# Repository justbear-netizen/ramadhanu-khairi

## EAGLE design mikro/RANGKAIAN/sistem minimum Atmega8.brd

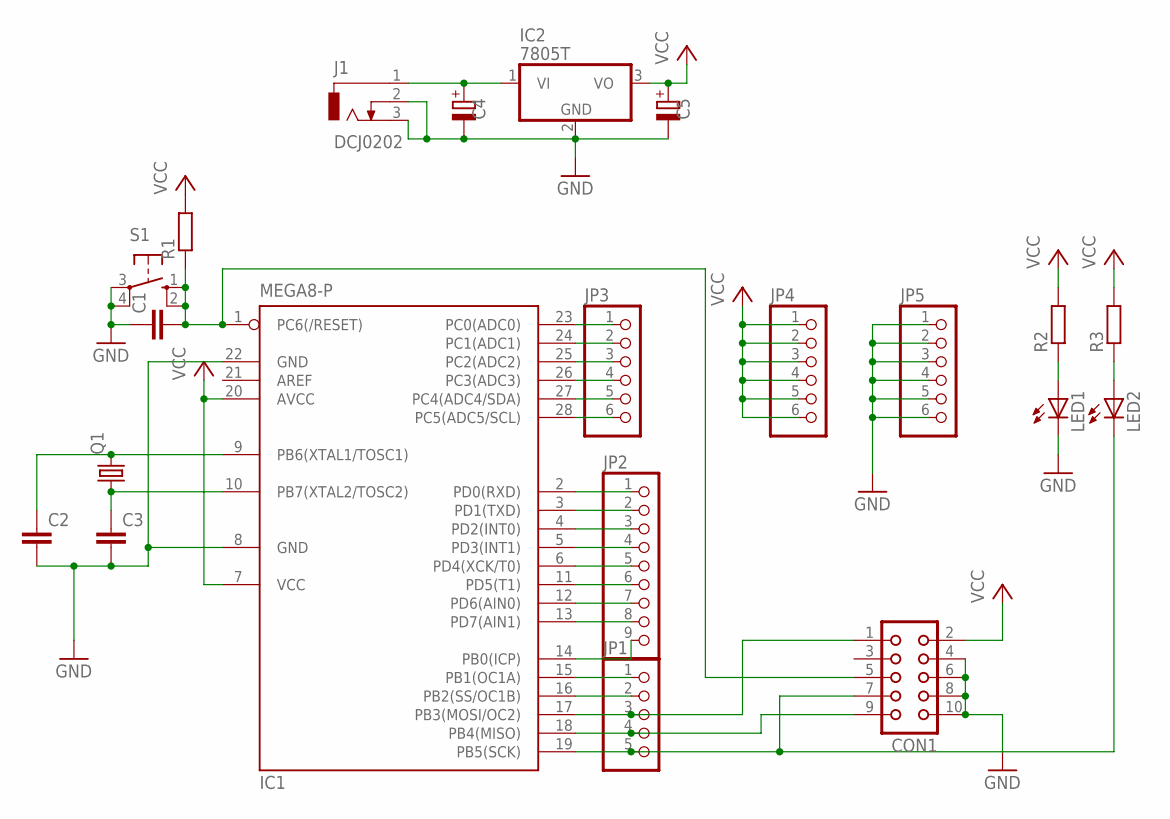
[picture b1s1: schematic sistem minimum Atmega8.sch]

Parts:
C1, C2, C3: C-EU025-030X050; C025-030X050
C4, C5: CPOL-EUE2.5-6; E2,5-6
CON1: CON10
IC1: MEGA8-P; DIL28-3
IC2: 7805T; TO220H
J1: DCJ0202
JP1: PINHD-1X5; 1X05
JP2: PINHD-1X9; 1X09
JP3, JP4, JP5: PINHD-1X6; 1X06
LED1, LED2: LED3MM
Q1: CRYSTALHC49U-V; HC49U-V
R1, R2, R3: R-EU_0204/7; 0204/7
S1: 10-XX; B3F-10XX

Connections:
GND: C1.1, C2.2, C3.2, C4.-, C5.-, CON1.4, CON1.6, CON1.8, CON1.10, IC1.8 (GND), IC1.22 (GND), IC2.2 (GND), J1.2, J1.3, JP5.1, JP5.2, JP5.3, JP5.4, JP5.5, JP5.6, LED1.K (C), S1.3, S1.4 (P1)
unnamed: IC1.2 (PD0(RXD)), JP2.1
unnamed: IC1.3 (PD1(TXD)), JP2.2
unnamed: IC1.4 (PD2(INT0)), JP2.3
unnamed: IC1.5 (PD3(INT1)), JP2.4
unnamed: IC1.6 (PD4(XCK/T0)), JP2.5
unnamed: IC1.11 (PD5(T1)), JP2.6
unnamed: IC1.12 (PD6(AIN0)), JP2.7
unnamed: IC1.13 (PD7(AIN1)), JP2.8
unnamed: IC1.14 (PB0(ICP)), JP2.9
unnamed: IC1.15 (PB1(OC1A)), JP1.1
unnamed: IC1.16 (PB2(SS/OC1B)), JP1.2
unnamed: CON1.1, IC1.17 (PB3(MOSI/OC2)), JP1.3
unnamed: CON1.9, IC1.18 (PB4(MISO)), JP1.4
unnamed: C4.+, IC2.1 (VI), J1.1
unnamed: IC1.23 (PC0(ADC0)), JP3.1
unnamed: IC1.24 (PC1(ADC1)), JP3.2
unnamed: IC1.25 (PC2(ADC2)), JP3.3
unnamed: IC1.26 (PC3(ADC3)), JP3.4
unnamed: IC1.27 (PC4(ADC4/SDA)), JP3.5
unnamed: IC1.28 (PC5(ADC5/SCL)), JP3.6
unnamed: C2.1, IC1.9 (PB6(XTAL1/TOSC1)), Q1.2
unnamed: C3.1, IC1.10 (PB7(XTAL2/TOSC2)), Q1.1
unnamed: C1.2, CON1.5, IC1.1 (PC6(/RESET)), R1.1, S1.1 (S), S1.2 (S1)
unnamed: LED2.A, R3.1
unnamed: CON1.7, IC1.19 (PB5(SCK)), JP1.5, LED2.K (C)
unnamed: LED1.A, R2.1
VCC: C5.+, CON1.2, IC1.7 (VCC), IC1.20 (AVCC), IC2.3 (VO), JP4.1, JP4.2, JP4.3, JP4.4, JP4.5, JP4.6, R1.2, R2.2, R3.2

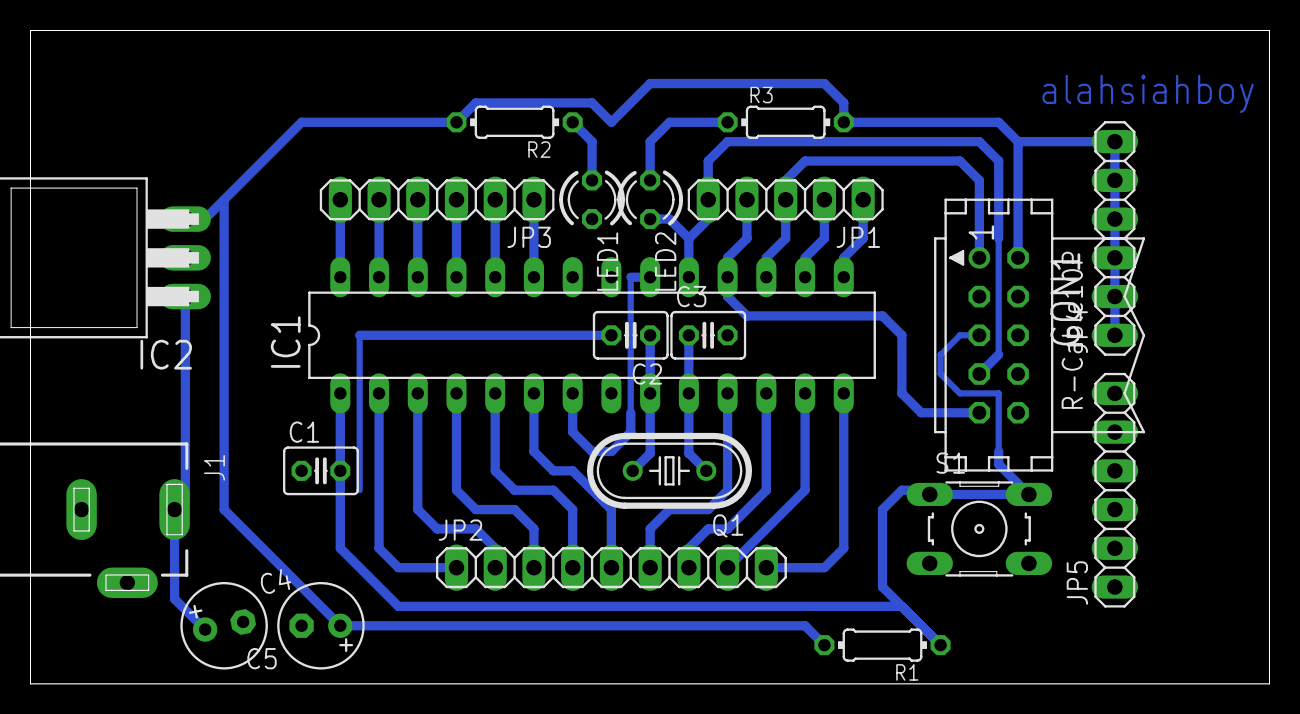
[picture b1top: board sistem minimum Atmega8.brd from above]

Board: 2 copper layers, 81.3 x 42.9 mm, 21 parts (0 on the bottom side), 28 nets.

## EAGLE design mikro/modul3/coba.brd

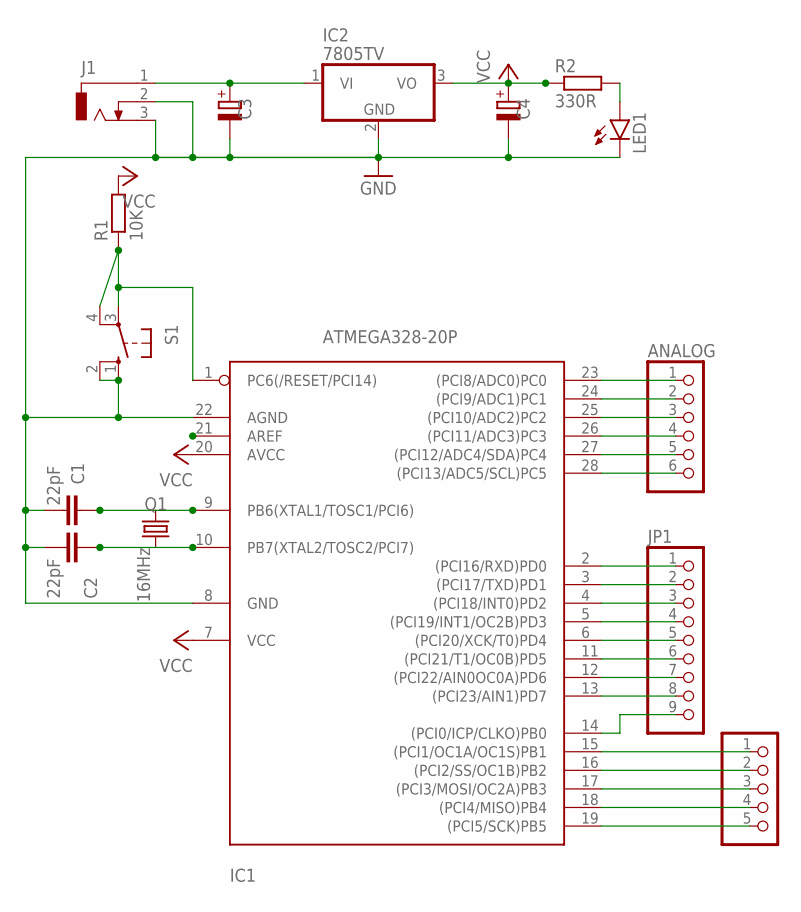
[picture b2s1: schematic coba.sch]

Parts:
ANALOG: PINHD-1X6; 1X06
C1, C2: 22pF; C025-024X044
C3, C4: CPOL-EUE2.5-6; E2,5-6
DIGITAL2: PINHD-1X5; 1X05
IC1: ATMEGA328-20P; DIL28-3
IC2: 7805TV; TO220V
J1: DCJ0303
JP1: PINHD-1X9; 1X09
LED1: LED3MM
Q1: 16MHz; HC49U70
R1: 10K; 0207/10
R2: 330R; 0207/10
S1: 10-XX; B3F-10XX

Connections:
ANALOG: ANALOG.2, IC1.24 ((PCI9/ADC1)PC1)
GND: C1.2, C2.2, C3.-, C4.-, IC1.8 (GND), IC1.22 (AGND), IC2.2 (GND), J1.2, J1.3, LED1.K (C), S1.1 (S), S1.2 (S1)
unnamed: C1.1, IC1.9 (PB6(XTAL1/TOSC1/PCI6)), Q1.1
unnamed: C2.1, IC1.10 (PB7(XTAL2/TOSC2/PCI7)), Q1.2
unnamed: ANALOG.1, IC1.23 ((PCI8/ADC0)PC0)
unnamed: C3.+, IC2.1 (VI), J1.1
unnamed: ANALOG.3, IC1.25 ((PCI10/ADC2)PC2)
unnamed: ANALOG.4, IC1.26 ((PCI11/ADC3)PC3)
unnamed: ANALOG.5, IC1.27 ((PCI12/ADC4/SDA)PC4)
unnamed: ANALOG.6, IC1.28 ((PCI13/ADC5/SCL)PC5)
unnamed: IC1.2 ((PCI16/RXD)PD0), JP1.1
unnamed: IC1.3 ((PCI17/TXD)PD1), JP1.2
unnamed: IC1.4 ((PCI18/INT0)PD2), JP1.3
unnamed: IC1.5 ((PCI19/INT1/OC2B)PD3), JP1.4
unnamed: IC1.6 ((PCI20/XCK/T0)PD4), JP1.5
unnamed: IC1.11 ((PCI21/T1/OC0B)PD5), JP1.6
unnamed: IC1.12 ((PCI22/AIN0OC0A)PD6), JP1.7
unnamed: IC1.13 ((PCI23/AIN1)PD7), JP1.8
unnamed: DIGITAL2.1, IC1.15 ((PCI1/OC1A/OC1S)PB1)
unnamed: DIGITAL2.2, IC1.16 ((PCI2/SS/OC1B)PB2)
unnamed: DIGITAL2.3, IC1.17 ((PCI3/MOSI/OC2A)PB3)
unnamed: DIGITAL2.4, IC1.18 ((PCI4/MISO)PB4)
unnamed: DIGITAL2.5, IC1.19 ((PCI5/SCK)PB5)
unnamed: IC1.14 ((PCI0/ICP/CLKO)PB0), JP1.9
unnamed: LED1.A, R2.2
VCC: C4.+, IC1.1 (PC6(/RESET/PCI14)), IC1.7 (VCC), IC1.20 (AVCC), IC1.21 (AREF), IC2.3 (VO), R1.1, R1.2, R2.1, S1.3, S1.4 (P1)

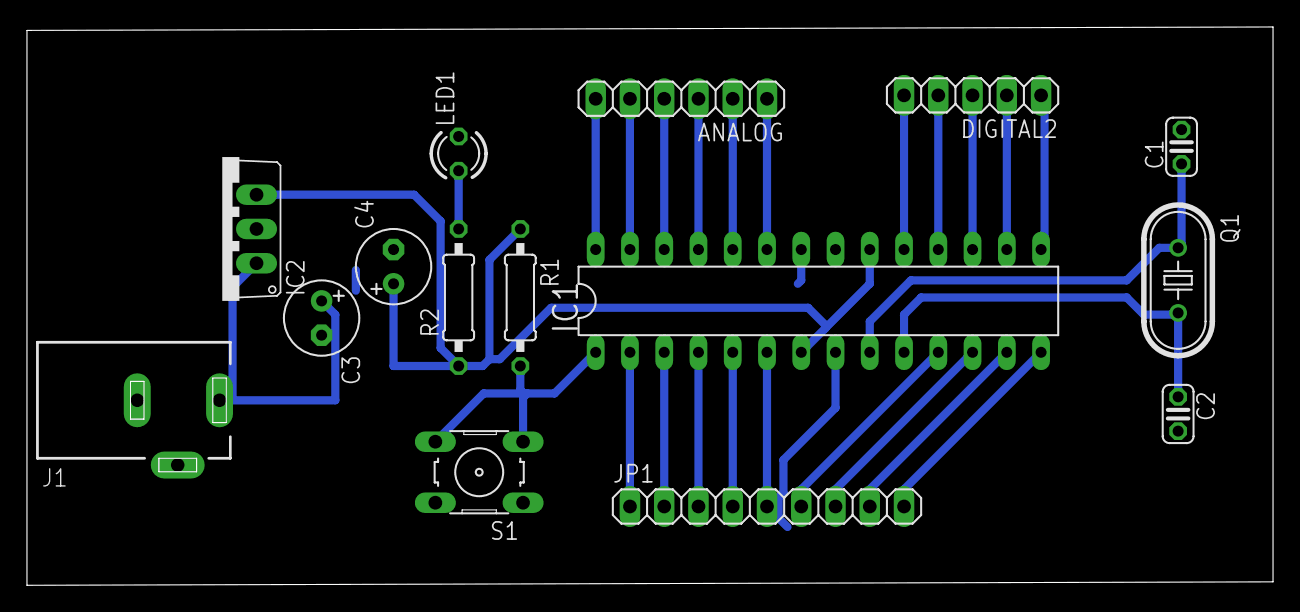
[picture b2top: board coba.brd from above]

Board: 2 copper layers, 92.4 x 41.4 mm, 15 parts (0 on the bottom side), 26 nets.

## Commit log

2021-03-04 ini coba
2021-03-04 hapus
2021-03-04 masukin jurnal
2021-03-07 coba
2021-03-07 Add files via upload
    codingan 1
2021-03-07 codingan 2
2021-03-07 sisken
2021-03-07 Create modul pwm
2021-03-07 Create modul
2021-03-07 Modul PWM
2021-03-07 Create a
2021-03-07 modul 1
2021-03-07 Add files via upload
    upload
2021-03-08 mikro modul3
2021-03-08 Add files via upload
    proteus motor
2021-03-08 kasus modul 2
2021-03-08 proteus modul 2
2021-03-09 modul3 interface
2021-03-09 codingan modul 1
2021-03-09 PWM ERROR DETECTION MEMORY
2021-03-09 PWM dengan Error Detection Memory
2021-03-17 update modul4
2021-03-17 proteusnya lupa hehehehe
2021-03-17 nomer 3
2021-03-17 nomer 5 sama 6
2021-03-17 proteus dan code nya
2021-03-18 upload lagi nich
2021-03-18 pdf upload
2021-03-18 upload lagiiii
2021-03-25 modul 5
2021-03-25 sisianya
2021-03-30 asdasdsad
2021-03-30 codingan modul 6
2021-03-30 proteus mod 6
2021-03-30 tugas mod 6
2021-04-03 up to date
2021-04-05 mod7
2021-04-05 laporan modul 7
2021-04-06 rangkain
2021-04-11 modul 8 yooo
2021-04-13 Create x
2021-04-13 codingan
2021-04-13 proteus
2021-04-13 BACA
2021-04-13 laporan
2021-04-14 Update baca
2021-04-14 praktikum mandiri khairi
2021-04-18 modul13
2021-04-18 upload
2021-04-18 deleate
2021-04-18 upload modul12
2021-04-25 proteus mod 9
2021-04-25 codingan mod 9
2021-04-25 laporan mod9
2021-05-03 proteusnya
2021-05-03 code nya
2021-05-14 modul 4
2021-06-03 Proposal Tugas Besar Skenario 1
2021-06-04 Update proposal tubes
